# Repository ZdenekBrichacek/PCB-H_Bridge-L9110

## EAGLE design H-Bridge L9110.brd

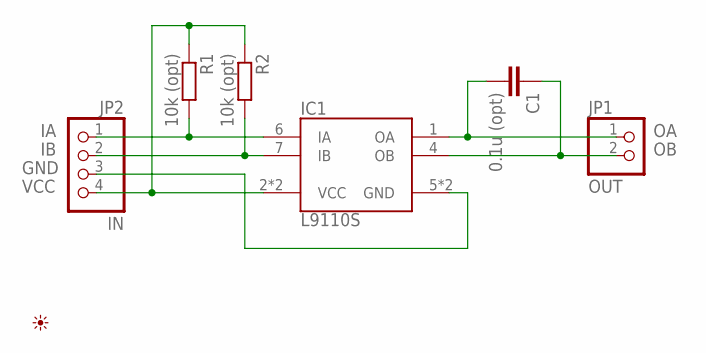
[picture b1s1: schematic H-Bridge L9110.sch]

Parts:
C1: 0.1u (opt); C0805K
IC1: L9110S; SO8
JP1: OUT; 1X02
JP2: IN; 1X04
PICTO1: PICTO_1
R1, R2: 10k (opt); R0603

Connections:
GND: IC1.5 (GND), IC1.8 (GND), JP2.3
IA: IC1.6 (IA), JP2.1, R1.2
IB: IC1.7 (IB), JP2.2, R2.2
OA: C1.2, IC1.1 (OA), JP1.1
OB: C1.1, IC1.4 (OB), JP1.2
VCC: IC1.2 (VCC), IC1.3 (VCC), JP2.4, R1.1, R2.1

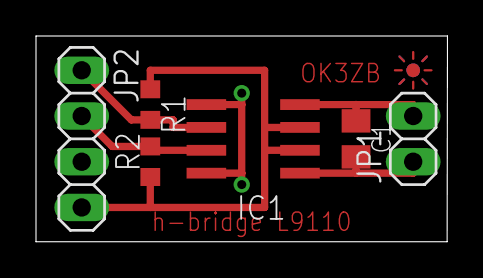
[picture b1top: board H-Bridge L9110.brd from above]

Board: 2 copper layers, 22.9 x 11.4 mm, 7 parts (0 on the bottom side), 6 nets.

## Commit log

2018-09-30 Change visibility of layers
